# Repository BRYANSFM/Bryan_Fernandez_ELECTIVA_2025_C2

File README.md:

# Bryan_Fernandez_ELECTIVA_2025_C2

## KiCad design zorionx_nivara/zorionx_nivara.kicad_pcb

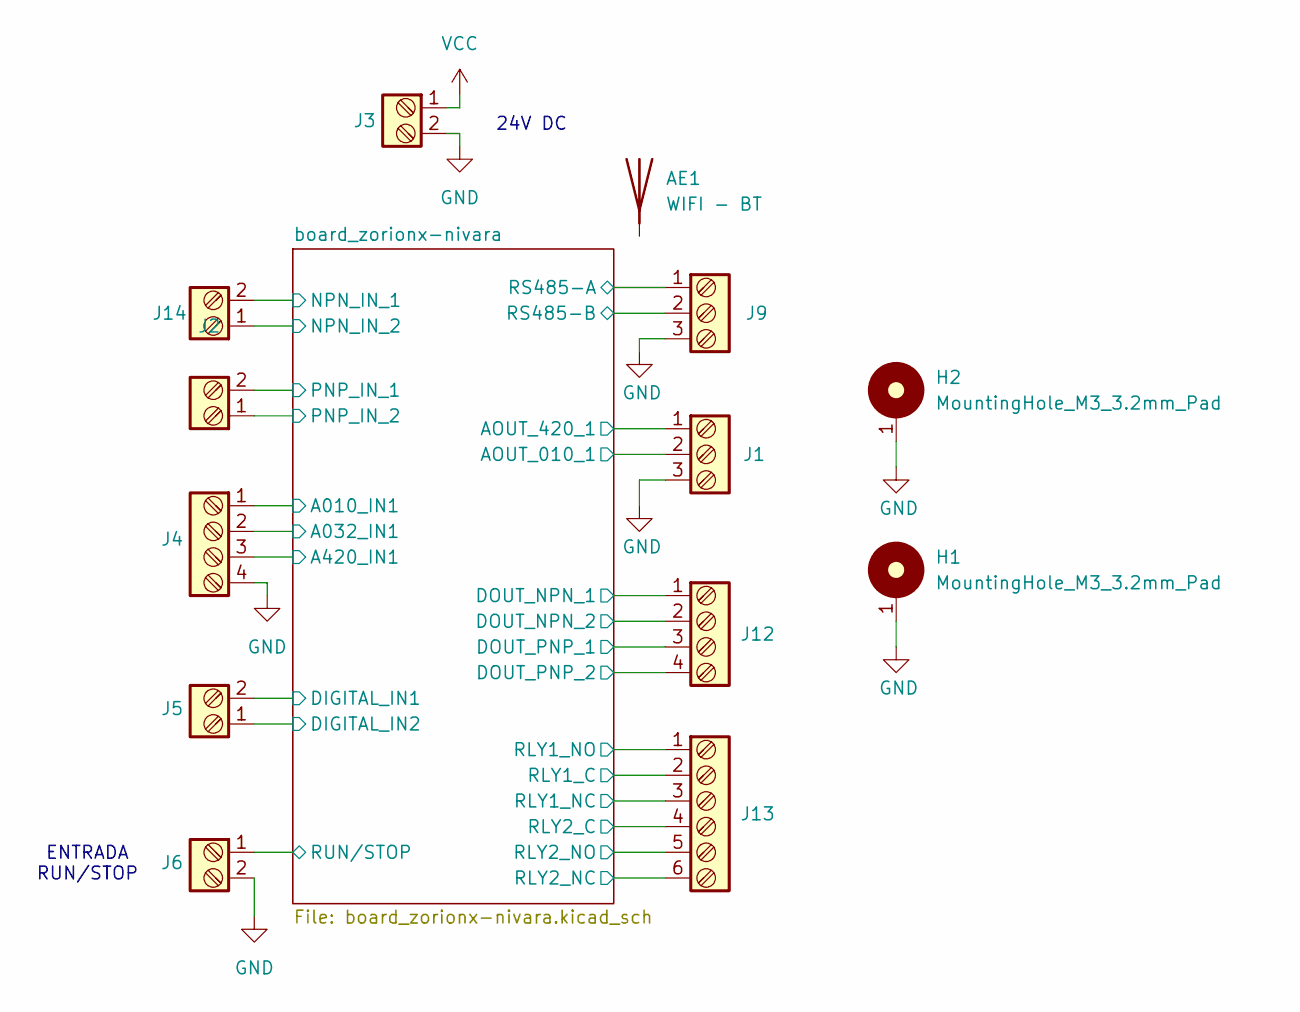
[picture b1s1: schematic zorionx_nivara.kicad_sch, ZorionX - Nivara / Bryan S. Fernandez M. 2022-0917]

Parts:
AE1: WIFI - BT
H1, H2: MountingHole_M3_3.2mm_Pad; MountingHole_3.2mm_Pad
J1: Salidas Analogicas; TerminalBlock_Phoenix_PT-1,5-3-5.0-H_1x03_P5.00mm_Horizontal
J2: Entrada PNP; TerminalBlock_Phoenix_PT-1,5-2-5.0-H_1x02_P5.00mm_Horizontal
J3: Alimentacion; TerminalBlock_Phoenix_PT-1,5-2-5.0-H_1x02_P5.00mm_Horizontal
J4: Entradas Analogicas; TerminalBlock_Phoenix_PT-1,5-4-5.0-H_1x04_P5.00mm_Horizontal
J5: Entradas digitales; TerminalBlock_Phoenix_PT-1,5-2-5.0-H_1x02_P5.00mm_Horizontal
J6: RUN/STOP; TerminalBlock_Phoenix_PT-1,5-2-5.0-H_1x02_P5.00mm_Horizontal
J9: RS-485; TerminalBlock_Phoenix_PT-1,5-3-5.0-H_1x03_P5.00mm_Horizontal
J12: Salidas NPN/PNP; TerminalBlock_Phoenix_PT-1,5-4-5.0-H_1x04_P5.00mm_Horizontal
J13: Reles; TerminalBlock_Phoenix_PT-1,5-6-5.0-H_1x06_P5.00mm_Horizontal
J14: Entrada NPN; TerminalBlock_Phoenix_PT-1,5-2-5.0-H_1x02_P5.00mm_Horizontal

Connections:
/board_zorionx-nivara/A010_IN1: J4.1; also elsewhere on the board
/board_zorionx-nivara/A032_IN1: J4.2; also elsewhere on the board
/board_zorionx-nivara/A420_IN1: J4.3; also elsewhere on the board
/board_zorionx-nivara/AOUT_010_1: J1.2; also elsewhere on the board
/board_zorionx-nivara/AOUT_420_1: J1.1; also elsewhere on the board
/board_zorionx-nivara/DIGITAL_IN1: J5.2; also elsewhere on the board
/board_zorionx-nivara/DIGITAL_IN2: J5.1; also elsewhere on the board
/board_zorionx-nivara/DOUT_NPN_1: J12.1; also elsewhere on the board
/board_zorionx-nivara/DOUT_NPN_2: J12.2; also elsewhere on the board
/board_zorionx-nivara/DOUT_PNP_1: J12.3; also elsewhere on the board
/board_zorionx-nivara/DOUT_PNP_2: J12.4; also elsewhere on the board
/board_zorionx-nivara/NPN_IN_1: J14.2; also elsewhere on the board
/board_zorionx-nivara/NPN_IN_2: J14.1; also elsewhere on the board
/board_zorionx-nivara/PNP_IN_1: J2.2; also elsewhere on the board
/board_zorionx-nivara/PNP_IN_2: J2.1; also elsewhere on the board
/board_zorionx-nivara/RLY1_C: J13.2; also elsewhere on the board
/board_zorionx-nivara/RLY1_NC: J13.3; also elsewhere on the board
/board_zorionx-nivara/RLY1_NO: J13.1; also elsewhere on the board
/board_zorionx-nivara/RLY2_C: J13.4; also elsewhere on the board
/board_zorionx-nivara/RLY2_NC: J13.6; also elsewhere on the board
/board_zorionx-nivara/RLY2_NO: J13.5; also elsewhere on the board
/board_zorionx-nivara/RS485-A: J9.1; also elsewhere on the board
/board_zorionx-nivara/RS485-B: J9.2; also elsewhere on the board
/board_zorionx-nivara/RUN/STOP: J6.1; also elsewhere on the board
GND: H1.1, H2.1, J1.3, J3.2, J4.4, J6.2, J9.3; also elsewhere on the board
VCC: J3.1; also elsewhere on the board

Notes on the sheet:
ENTRADA RUN/STOP
24V DC

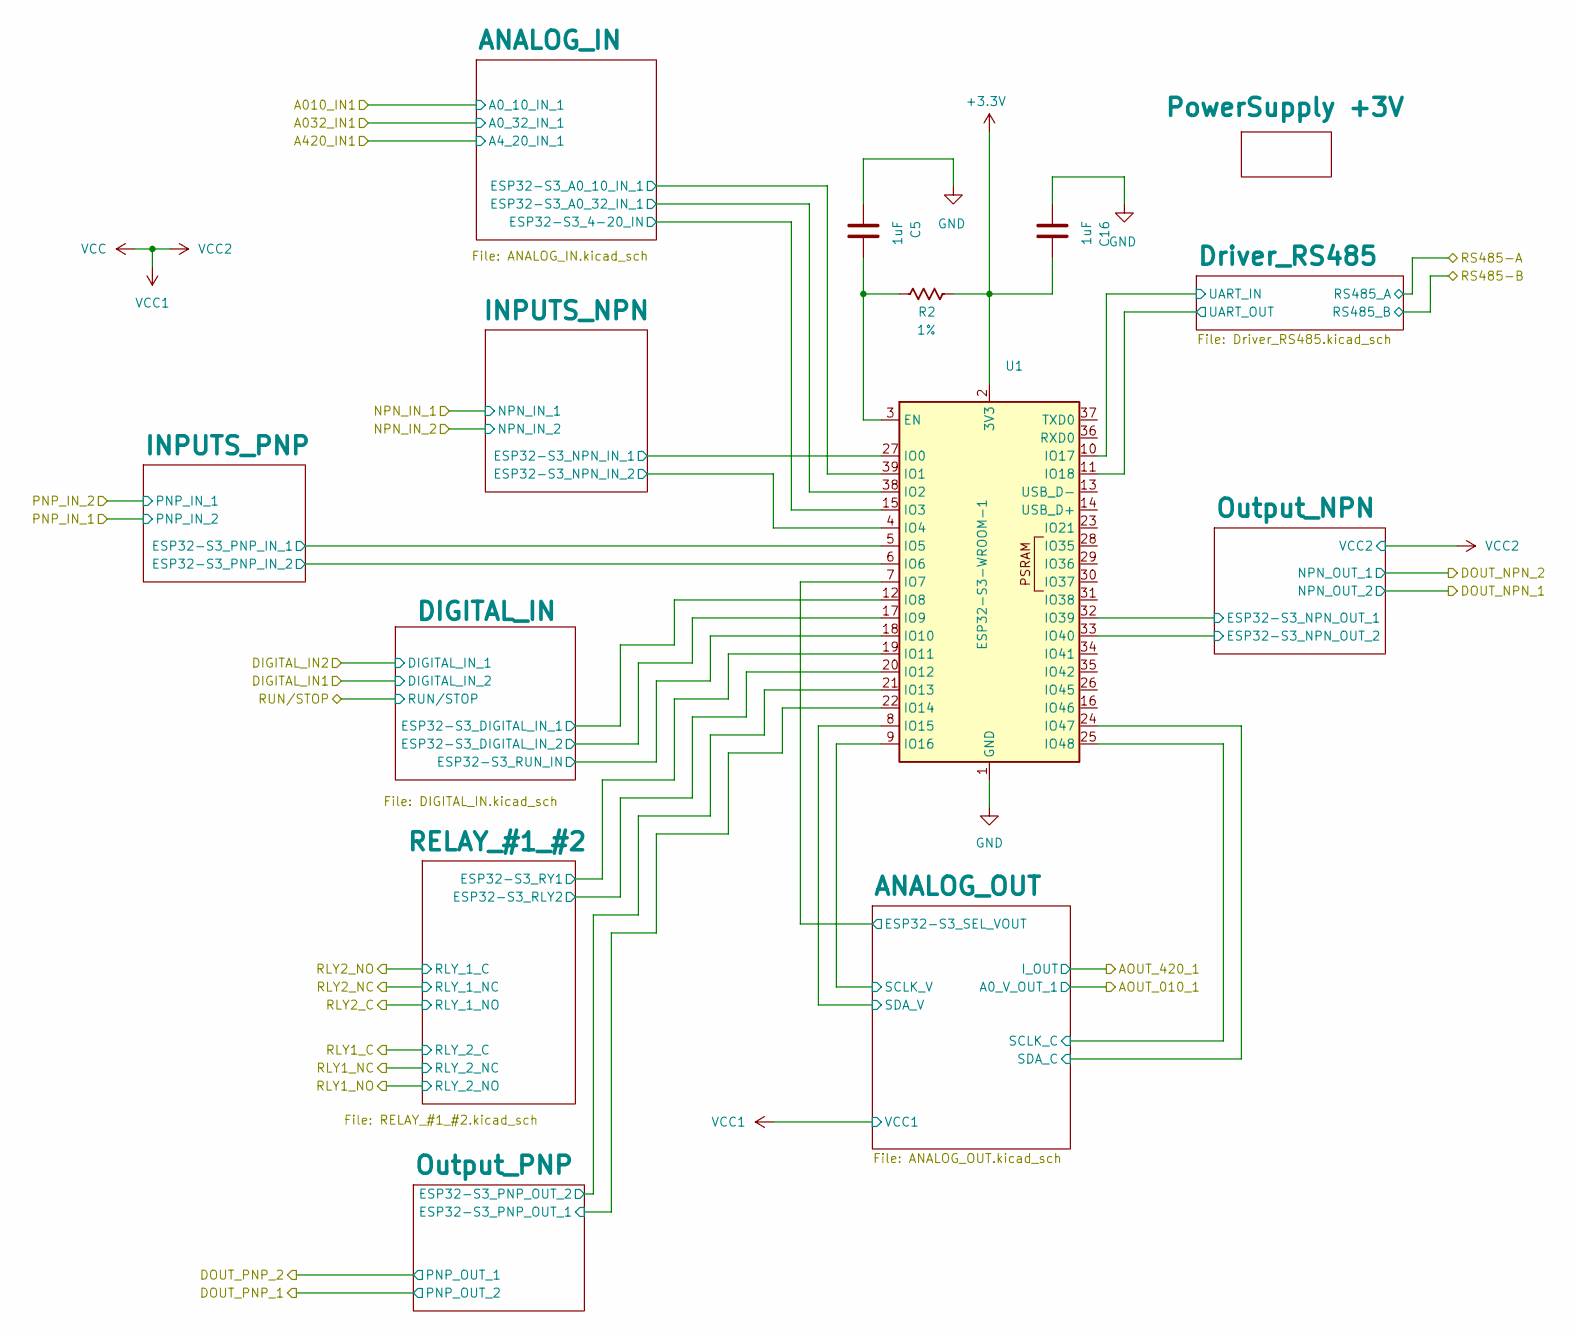
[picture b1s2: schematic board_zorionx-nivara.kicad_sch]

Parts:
C5, C16: 1uF; C_0603_1608Metric
R2: R_0603_1608Metric; Tolerancia 1%
U1: ESP32-S3-WROOM-1

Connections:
+3.3V: C16.1, R2.1, U1.2 (3V3); also elsewhere on the board
/board_zorionx-nivara/ANALOG_IN/ESP32-S3_4-20_IN: U1.15 (IO3); also elsewhere on the board
/board_zorionx-nivara/ANALOG_IN/ESP32-S3_A0_10_IN_1: U1.39 (IO1); also elsewhere on the board
/board_zorionx-nivara/ANALOG_IN/ESP32-S3_A0_32_IN_1: U1.38 (IO2); also elsewhere on the board
/board_zorionx-nivara/ANALOG_OUT/ESP32-S3_SEL_VOUT: U1.7 (IO7); also elsewhere on the board
/board_zorionx-nivara/ANALOG_OUT/SCLK_C: U1.25 (IO48); also elsewhere on the board
/board_zorionx-nivara/ANALOG_OUT/SCLK_V: U1.9 (IO16); also elsewhere on the board
/board_zorionx-nivara/ANALOG_OUT/SDA_C: U1.24 (IO47); also elsewhere on the board
/board_zorionx-nivara/ANALOG_OUT/SDA_V: U1.8 (IO15); also elsewhere on the board
/board_zorionx-nivara/DIGITAL_IN/ESP32-S3_DIGITAL_IN_1: U1.12 (IO8); also elsewhere on the board
/board_zorionx-nivara/DIGITAL_IN/ESP32-S3_DIGITAL_IN_2: U1.17 (IO9); also elsewhere on the board
/board_zorionx-nivara/DIGITAL_IN/ESP32-S3_RUN_IN: U1.18 (IO10); also elsewhere on the board
/board_zorionx-nivara/Driver_RS485/UART_IN: U1.10 (IO17); also elsewhere on the board
/board_zorionx-nivara/Driver_RS485/UART_OUT: U1.11 (IO18); also elsewhere on the board
/board_zorionx-nivara/INPUTS_NPN/ESP32-S3_NPN_IN_1: U1.27 (IO0); also elsewhere on the board
/board_zorionx-nivara/INPUTS_NPN/ESP32-S3_NPN_IN_2: U1.4 (IO4); also elsewhere on the board
/board_zorionx-nivara/INPUTS_PNP/ESP32-S3_PNP_IN_1: U1.5 (IO5); also elsewhere on the board
/board_zorionx-nivara/INPUTS_PNP/ESP32-S3_PNP_IN_2: U1.6 (IO6); also elsewhere on the board
/board_zorionx-nivara/Output_NPN/ESP32-S3_NPN_OUT_1: U1.32 (IO39); also elsewhere on the board
/board_zorionx-nivara/Output_NPN/ESP32-S3_NPN_OUT_2: U1.33 (IO40); also elsewhere on the board
/board_zorionx-nivara/Output_PNP/ESP32-S3_PNP_OUT_1: U1.22 (IO14); also elsewhere on the board
/board_zorionx-nivara/Output_PNP/ESP32-S3_PNP_OUT_2: U1.21 (IO13); also elsewhere on the board
/board_zorionx-nivara/RELAY_#1_#2/ESP32-S3_RLY2: U1.20 (IO12); also elsewhere on the board
/board_zorionx-nivara/RELAY_#1_#2/ESP32-S3_RY1: U1.19 (IO11); also elsewhere on the board
GND: C5.2, C16.2, U1.1 (GND), U1.40 (GND), U1.41 (GND); also elsewhere on the board
unnamed: C5.1, R2.2, U1.3 (EN)

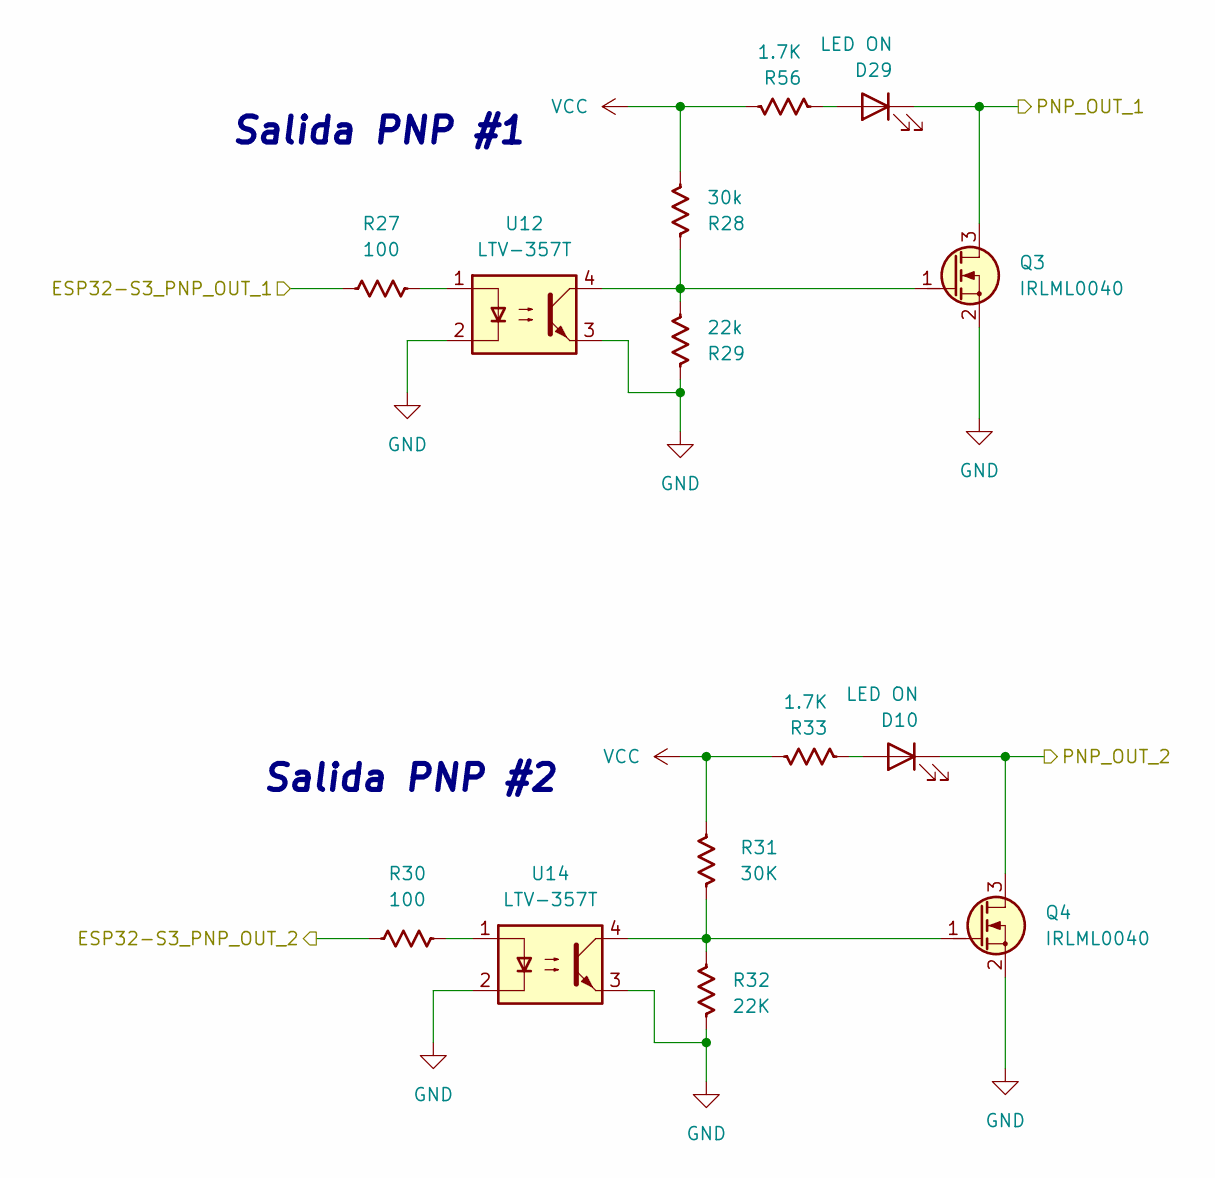
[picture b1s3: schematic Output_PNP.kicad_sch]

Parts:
D10, D29: LED ON; LED_0603_1608Metric
Q3, Q4: IRLML0040; SOT-23
R27, R30: 100; R_0603_1608Metric
R28: 30k; R_0603_1608Metric
R29: 22k; R_0603_1608Metric
R31: 30K; R_0603_1608Metric
R32: 22K; R_0603_1608Metric
R33, R56: 1.7K; R_0603_1608Metric
U12, U14: LTV-357T; SO-4_4.4x3.6mm_P2.54mm

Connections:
/board_zorionx-nivara/DOUT_PNP_1: D10.1 (K), Q4.3 (D); also elsewhere on the board
/board_zorionx-nivara/DOUT_PNP_2: D29.1 (K), Q3.3 (D); also elsewhere on the board
/board_zorionx-nivara/Output_PNP/ESP32-S3_PNP_OUT_1: R27.1; also elsewhere on the board
/board_zorionx-nivara/Output_PNP/ESP32-S3_PNP_OUT_2: R30.1; also elsewhere on the board
GND: Q3.2 (S), Q4.2 (S), R29.1, R32.1, U12.2, U12.3, U14.2, U14.3; also elsewhere on the board
unnamed: D10.2 (A), R33.2
unnamed: D29.2 (A), R56.2
unnamed: Q3.1 (G), R28.1, R29.2, U12.4
unnamed: Q4.1 (G), R31.1, R32.2, U14.4
unnamed: R27.2, U12.1
unnamed: R30.2, U14.1
VCC: R28.2, R31.2, R33.1, R56.1; also elsewhere on the board

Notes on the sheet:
Salida PNP #1
Salida PNP #2

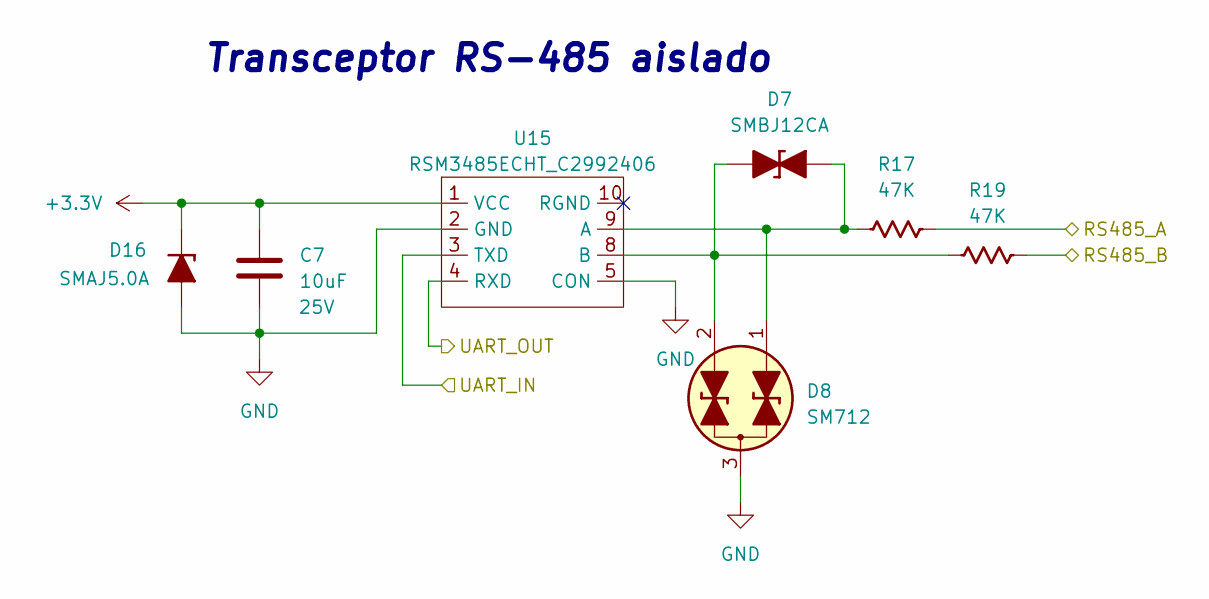
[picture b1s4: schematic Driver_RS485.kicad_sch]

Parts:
C7: 10uF; C_0603_1608Metric
D7: SMBJ12CA; D_SMB_TVS
D8: SM712; SOT-23
D16: SMAJ5.0A; D_SMA
R17, R19: 47K; R_0603_1608Metric
U15: RSM3485ECHT_C2992406; YLPTEC RSM3485ECHT

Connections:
+3.3V: C7.1, D16.1 (K), U15.1 (VCC); also elsewhere on the board
/board_zorionx-nivara/Driver_RS485/UART_IN: U15.3 (TXD); also elsewhere on the board
/board_zorionx-nivara/Driver_RS485/UART_OUT: U15.4 (RXD); also elsewhere on the board
/board_zorionx-nivara/RS485-A: R17.2; also elsewhere on the board
/board_zorionx-nivara/RS485-B: R19.2; also elsewhere on the board
GND: C7.2, D8.3 (Com), D16.2 (A), U15.2 (GND), U15.5 (CON); also elsewhere on the board
unnamed: D7.2 (A), D8.1 (A1), R17.1, U15.9 (A)
unnamed: D7.1 (K), D8.2 (A2), R19.1, U15.8 (B)

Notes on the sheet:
Transceptor RS-485 aislado

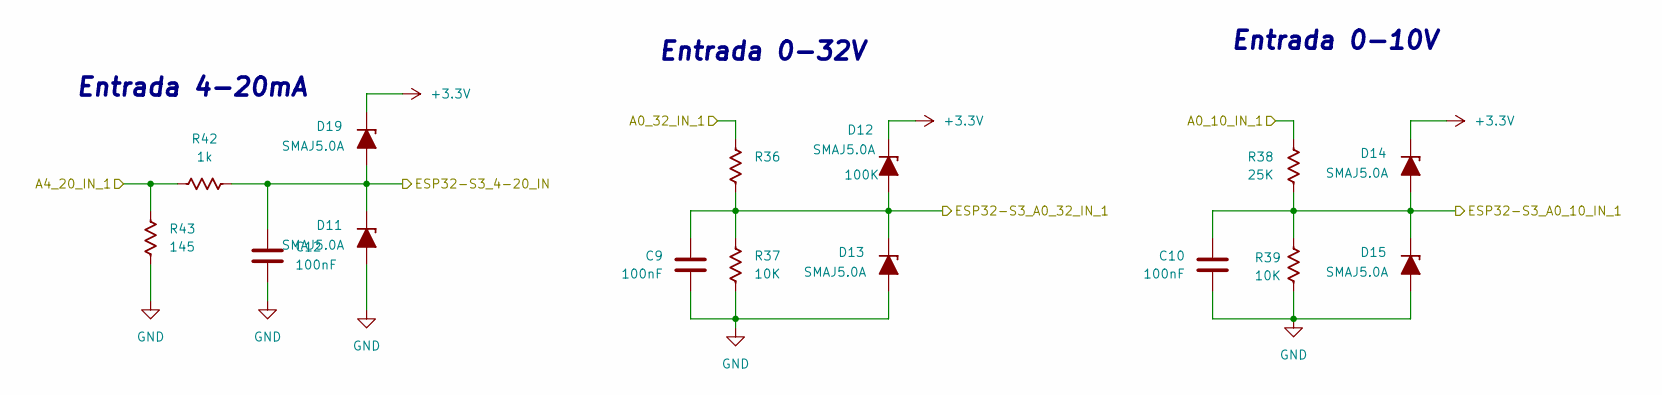
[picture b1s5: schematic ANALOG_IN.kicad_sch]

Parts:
C9, C10, C12: 100nF; C_0603_1608Metric; Voltage 10V
D11, D12, D13, D14, D15, D19: SMAJ5.0A; D_SMA
R36: 100K; R_0603_1608Metric
R37, R39: 10K; R_0603_1608Metric
R38: 25K; R_0603_1608Metric
R42: 1k; R_0603_1608Metric
R43: 145; R_0805_2012Metric

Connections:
+3.3V: D12.1 (K), D14.1 (K), D19.1 (K); also elsewhere on the board
/board_zorionx-nivara/A010_IN1: R38.2; also elsewhere on the board
/board_zorionx-nivara/A032_IN1: R36.2; also elsewhere on the board
/board_zorionx-nivara/A420_IN1: R42.1, R43.1; also elsewhere on the board
/board_zorionx-nivara/ANALOG_IN/ESP32-S3_4-20_IN: C12.1, D11.1 (K), D19.2 (A), R42.2; also elsewhere on the board
/board_zorionx-nivara/ANALOG_IN/ESP32-S3_A0_10_IN_1: C10.1, D14.2 (A), D15.1 (K), R38.1, R39.2; also elsewhere on the board
/board_zorionx-nivara/ANALOG_IN/ESP32-S3_A0_32_IN_1: C9.1, D12.2 (A), D13.1 (K), R36.1, R37.2; also elsewhere on the board
GND: C9.2, C10.2, C12.2, D11.2 (A), D13.2 (A), D15.2 (A), R37.1, R39.1, R43.2; also elsewhere on the board

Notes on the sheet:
Entrada 0-10V
Entrada 0-32V
Entrada 4-20mA

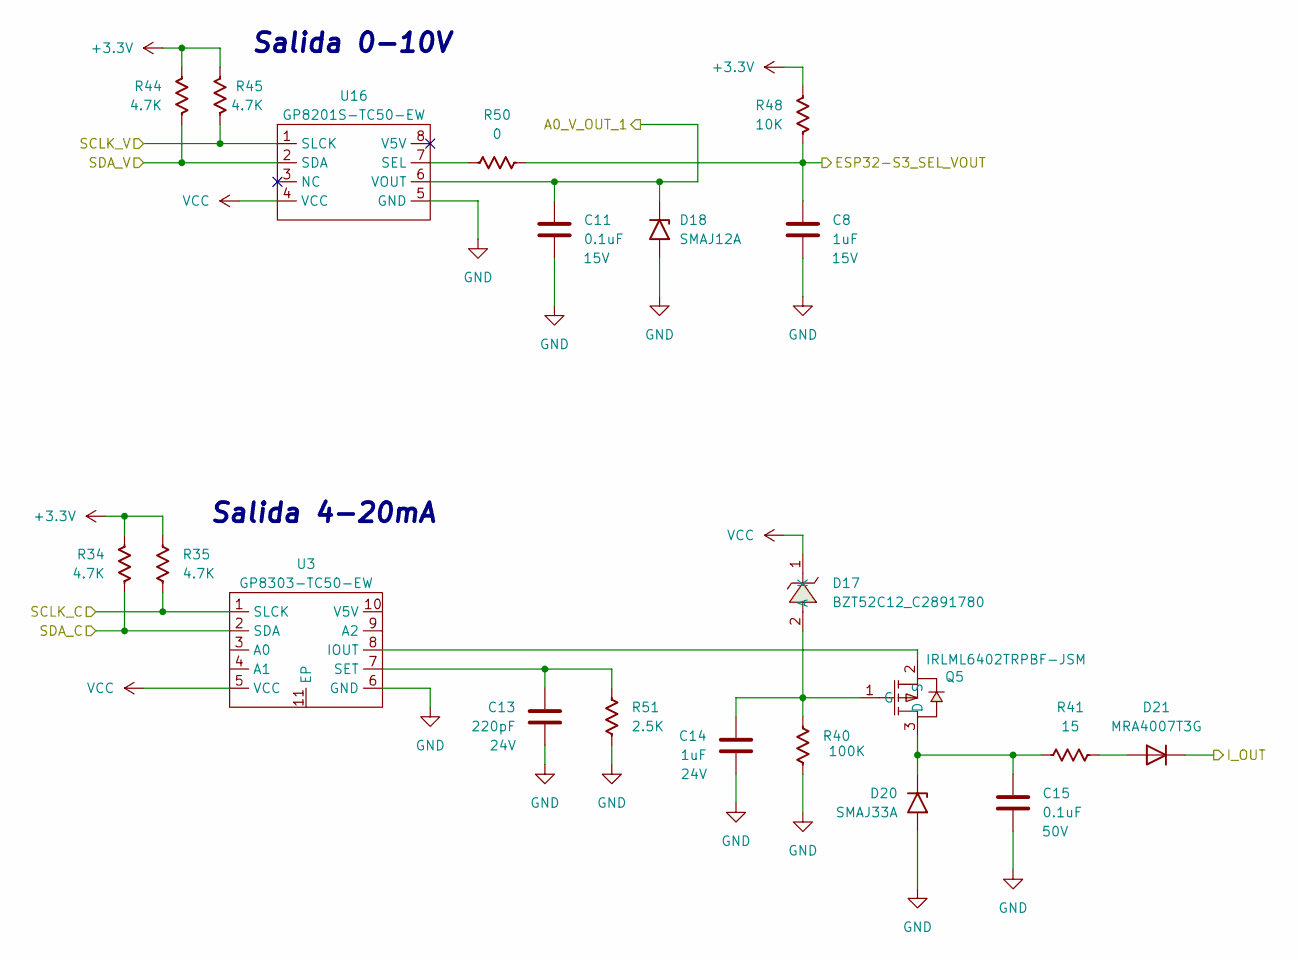
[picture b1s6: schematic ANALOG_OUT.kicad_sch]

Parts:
C8, C14: 1uF; C_0603_1608Metric
C11, C15: 0.1uF; C_0603_1608Metric
C13: 220pF; C_0603_1608Metric
D17: BZT52C12_C2891780; D_SOD-123; LCSC Part C2891780
D18: SMAJ12A; D_SMA
D20: SMAJ33A; D_SMA
D21: MRA4007T3G; D_SMA
Q5: IRLML6402TRPBF-JSM; SOT-23; LCSC Part C18190991
R34, R35, R44, R45: 4.7K; R_0603_1608Metric
R40: 100K; R_0603_1608Metric
R41: 15; R_0805_2012Metric
R48: 10K; R_0603_1608Metric
R50: 0; R_0603_1608Metric
R51: 2.5K; R_0603_1608Metric
U3: GP8303-TC50-EW; SSOP-10_3.9x4.9mm_P1.00mm
U16: GP8201S-TC50-EW; SSOP-8_3.95x5.21x3.27mm_P1.27mm

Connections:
+3.3V: R34.1, R35.1, R44.1, R45.1, R48.1; also elsewhere on the board
/board_zorionx-nivara/ANALOG_OUT/ESP32-S3_SEL_VOUT: C8.1, R48.2, R50.2; also elsewhere on the board
/board_zorionx-nivara/ANALOG_OUT/SCLK_C: R35.2, U3.1 (SLCK); also elsewhere on the board
/board_zorionx-nivara/ANALOG_OUT/SCLK_V: R45.2, U16.1 (SLCK); also elsewhere on the board
/board_zorionx-nivara/ANALOG_OUT/SDA_C: R34.2, U3.2 (SDA); also elsewhere on the board
/board_zorionx-nivara/ANALOG_OUT/SDA_V: R44.2, U16.2 (SDA); also elsewhere on the board
/board_zorionx-nivara/AOUT_010_1: C11.1, D18.1 (A1), U16.6 (VOUT); also elsewhere on the board
/board_zorionx-nivara/AOUT_420_1: D21.1 (K); also elsewhere on the board
GND: C8.2, C11.2, C13.2, C14.2, C15.2, D18.2 (A2), D20.2 (A2), R40.2, R51.2, U3.6 (GND), U16.5 (GND); also elsewhere on the board
unnamed: C14.1, D17.2 (A), Q5.1 (G), R40.1
unnamed: C15.1, D20.1 (A1), Q5.3 (D), R41.1
unnamed: D21.2 (A), R41.2
unnamed: Q5.2 (S), U3.8 (IOUT)
unnamed: C13.1, R51.1, U3.7 (SET)
unnamed: R50.1, U16.7 (SEL)
VCC: D17.1 (K), U3.5 (VCC), U16.4 (VCC); also elsewhere on the board

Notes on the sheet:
Salida 0-10V
Salida 4-20mA

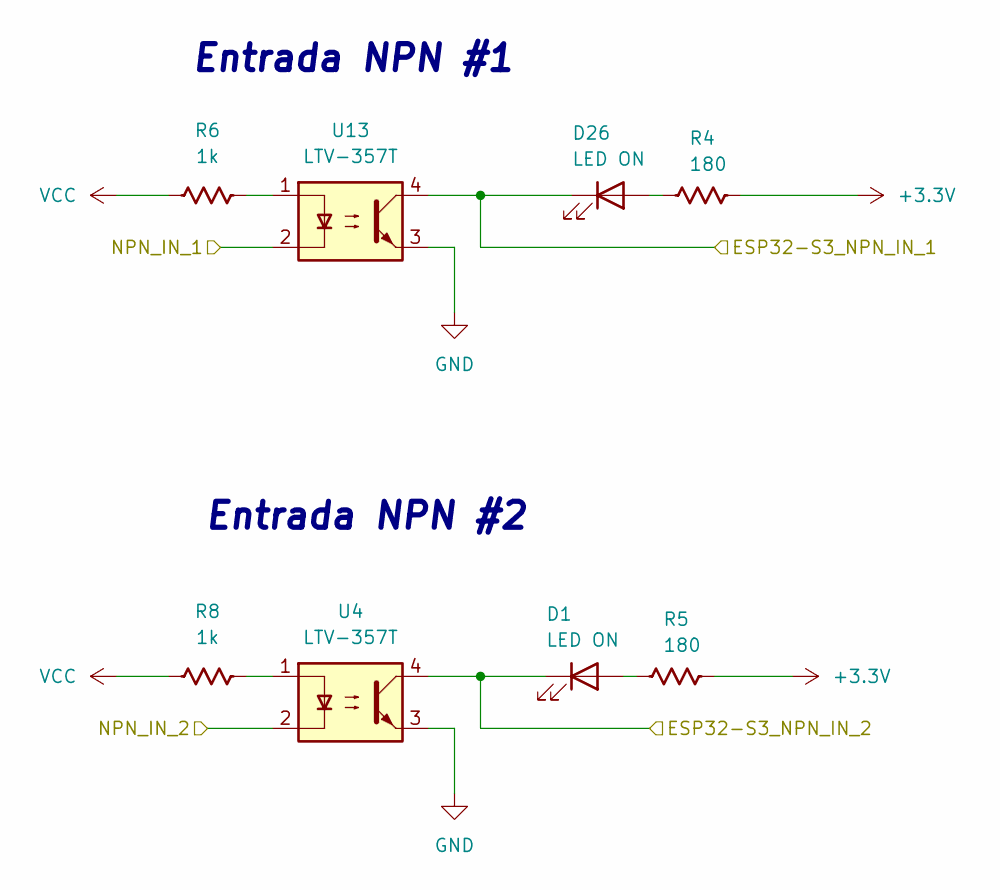
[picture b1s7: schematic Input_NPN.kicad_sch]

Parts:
D1, D26: LED ON; LED_0603_1608Metric
R4, R5: 180; R_0603_1608Metric
R6, R8: 1k; R_0603_1608Metric
U4, U13: LTV-357T; SO-4_4.4x3.6mm_P2.54mm

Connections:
+3.3V: R4.1, R5.1; also elsewhere on the board
/board_zorionx-nivara/INPUTS_NPN/ESP32-S3_NPN_IN_1: D26.1 (K), U13.4; also elsewhere on the board
/board_zorionx-nivara/INPUTS_NPN/ESP32-S3_NPN_IN_2: D1.1 (K), U4.4; also elsewhere on the board
/board_zorionx-nivara/NPN_IN_1: U13.2; also elsewhere on the board
/board_zorionx-nivara/NPN_IN_2: U4.2; also elsewhere on the board
GND: U4.3, U13.3; also elsewhere on the board
unnamed: D1.2 (A), R5.2
unnamed: D26.2 (A), R4.2
unnamed: R6.2, U13.1
unnamed: R8.2, U4.1
VCC: R6.1, R8.1; also elsewhere on the board

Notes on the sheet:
Entrada NPN #2
Entrada NPN #1

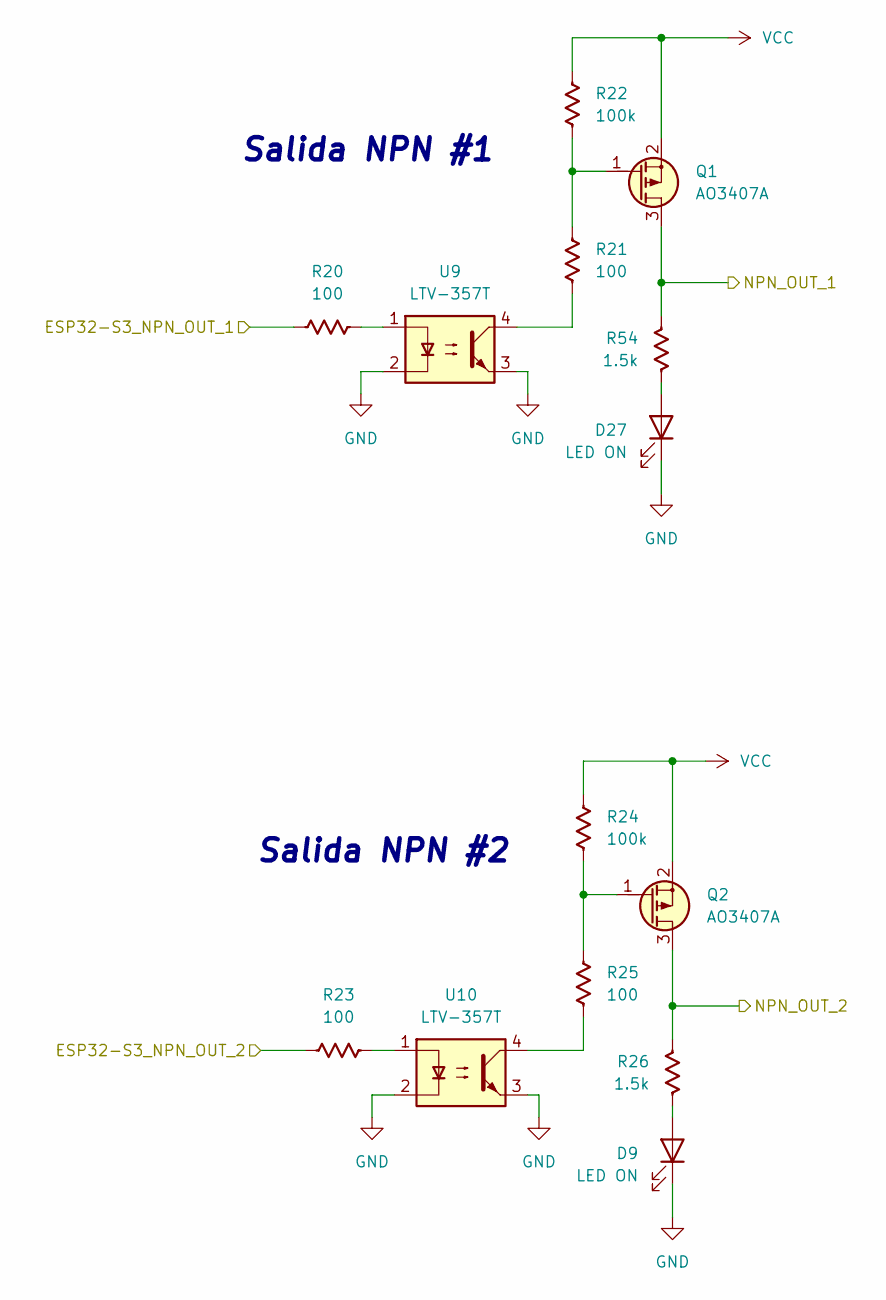
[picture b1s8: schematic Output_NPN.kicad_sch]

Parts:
D9, D27: LED ON; LED_0603_1608Metric
Q1, Q2: AO3407A; SOT-23
R20, R21, R23, R25: 100; R_0603_1608Metric
R22, R24: 100k; R_0603_1608Metric
R26, R54: 1.5k; R_0603_1608Metric
U9, U10: LTV-357T; SO-4_4.4x3.6mm_P2.54mm

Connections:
/board_zorionx-nivara/DOUT_NPN_1: Q2.3 (D), R26.1; also elsewhere on the board
/board_zorionx-nivara/DOUT_NPN_2: Q1.3 (D), R54.1; also elsewhere on the board
/board_zorionx-nivara/Output_NPN/ESP32-S3_NPN_OUT_1: R20.1; also elsewhere on the board
/board_zorionx-nivara/Output_NPN/ESP32-S3_NPN_OUT_2: R23.1; also elsewhere on the board
GND: D9.1 (K), D27.1 (K), U9.2, U9.3, U10.2, U10.3; also elsewhere on the board
unnamed: D9.2 (A), R26.2
unnamed: D27.2 (A), R54.2
unnamed: Q1.1 (G), R21.1, R22.2
unnamed: Q2.1 (G), R24.2, R25.1
unnamed: R20.2, U9.1
unnamed: R21.2, U9.4
unnamed: R23.2, U10.1
unnamed: R25.2, U10.4
VCC: Q1.2 (S), Q2.2 (S), R22.1, R24.1; also elsewhere on the board

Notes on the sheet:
Salida NPN #1
Salida NPN #2

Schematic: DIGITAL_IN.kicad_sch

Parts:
D4, D5, D6: LED ON; LED_0603_1608Metric
R12, R13, R15: 180; R_0603_1608Metric
R14, R16, R18: 1k; R_0603_1608Metric
U7, U8, U11: LTV-357T; SO-4_4.4x3.6mm_P2.54mm

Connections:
+3.3V: R12.1, R13.1, R15.1; also elsewhere on the board
/board_zorionx-nivara/DIGITAL_IN1: R14.1; also elsewhere on the board
/board_zorionx-nivara/DIGITAL_IN2: R16.1; also elsewhere on the board
/board_zorionx-nivara/DIGITAL_IN/ESP32-S3_DIGITAL_IN_1: D4.1 (K), U11.4; also elsewhere on the board
/board_zorionx-nivara/DIGITAL_IN/ESP32-S3_DIGITAL_IN_2: D5.1 (K), U7.4; also elsewhere on the board
/board_zorionx-nivara/DIGITAL_IN/ESP32-S3_RUN_IN: D6.1 (K), U8.4; also elsewhere on the board
/board_zorionx-nivara/RUN/STOP: R18.1; also elsewhere on the board
GND: U7.2, U7.3, U8.2, U8.3, U11.2, U11.3; also elsewhere on the board
unnamed: D4.2 (A), R12.2
unnamed: D5.2 (A), R13.2
unnamed: D6.2 (A), R15.2
unnamed: R14.2, U7.1
unnamed: R16.2, U11.1
unnamed: R18.2, U8.1

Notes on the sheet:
Entrada DIGITAL #1
Entrada DIGITAL #2
RUN/STOP

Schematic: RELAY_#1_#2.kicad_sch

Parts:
K1, K3: G5LE-1; Relay_SPDT_Omron-G5LE-1
U18: LANKE LK1802; SOT-23-6

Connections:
/board_zorionx-nivara/RELAY_#1_#2/ESP32-S3_RLY2: U18.4 (2B); also elsewhere on the board
/board_zorionx-nivara/RELAY_#1_#2/ESP32-S3_RY1: U18.3 (1B); also elsewhere on the board
/board_zorionx-nivara/RLY1_C: K1.1; also elsewhere on the board
/board_zorionx-nivara/RLY1_NC: K1.4; also elsewhere on the board
/board_zorionx-nivara/RLY1_NO: K1.3; also elsewhere on the board
/board_zorionx-nivara/RLY2_C: K3.3; also elsewhere on the board
/board_zorionx-nivara/RLY2_NC: K3.4; also elsewhere on the board
/board_zorionx-nivara/RLY2_NO: K3.1; also elsewhere on the board
GND: U18.2 (E); also elsewhere on the board
unnamed: K3.5, U18.1 (1C)
unnamed: K1.2, U18.6 (2C)
VCC: K1.5, K3.2, U18.5 (COM); also elsewhere on the board

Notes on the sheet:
Controlador RELAY #1, #2

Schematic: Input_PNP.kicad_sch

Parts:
D2, D3: LED ON; LED_0603_1608Metric
R7, R9: 180; R_0603_1608Metric
R10, R11: 1k; R_0603_1608Metric
U5, U6: LTV-357T; SO-4_4.4x3.6mm_P2.54mm

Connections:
+3.3V: R7.1, R9.1; also elsewhere on the board
/board_zorionx-nivara/INPUTS_PNP/ESP32-S3_PNP_IN_1: D2.1 (K), U5.4; also elsewhere on the board
/board_zorionx-nivara/INPUTS_PNP/ESP32-S3_PNP_IN_2: D3.1 (K), U6.4; also elsewhere on the board
/board_zorionx-nivara/PNP_IN_1: R11.1; also elsewhere on the board
/board_zorionx-nivara/PNP_IN_2: R10.1; also elsewhere on the board
GND: U5.2, U5.3, U6.2, U6.3; also elsewhere on the board
unnamed: D2.2 (A), R7.2
unnamed: D3.2 (A), R9.2
unnamed: R10.2, U5.1
unnamed: R11.2, U6.1

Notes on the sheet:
Entrada PNP #1
Entrada PNP #2

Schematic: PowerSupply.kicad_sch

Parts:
C1: 100pF; C_0603_1608Metric
C2, C6: 22uF; C_0805
C3: 10uF; C_1206_3216Metric
C4: 100nF; C_0603_1608Metric
JP1: SolderJumper_2_Open; SolderJumper-2_P1.3mm_Open_RoundedPad1.0x1.5mm
L1: 6.8uH; L_Chilisin_BMRA00040420; Part number SL0624-6R8M
R1: 196K; R_0603_1608Metric; Tolerancia 1%
R3: 62K; R_0603_1608Metric; Tolerancia 1%
TP1, TP2, TP3, TP4: TestPoint; TestPoint_THTPad_D1.0mm_Drill0.5mm
U2: AP63203WU; TSOT-23-6

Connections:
+3.3V: JP1.2 (B), TP4.1; also elsewhere on the board
/board_zorionx-nivara/PowerSupply +3V/sw: C4.2, L1.2, U2.5 (SW)
/board_zorionx-nivara/PowerSupply +3V/vout: C1.1, C2.1, C6.1, JP1.1 (A), L1.1, R1.1, TP1.1
GND: C2.2, C3.2, C6.2, R3.2, U2.4 (GND); also elsewhere on the board
unnamed: C4.1, U2.6 (BST)
unnamed: C1.2, R1.2, R3.1, TP2.1, U2.1 (FB)
VCC: C3.1, TP3.1, U2.2 (EN), U2.3 (IN); also elsewhere on the board

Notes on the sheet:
ic AP63203
Regulador 3.3V

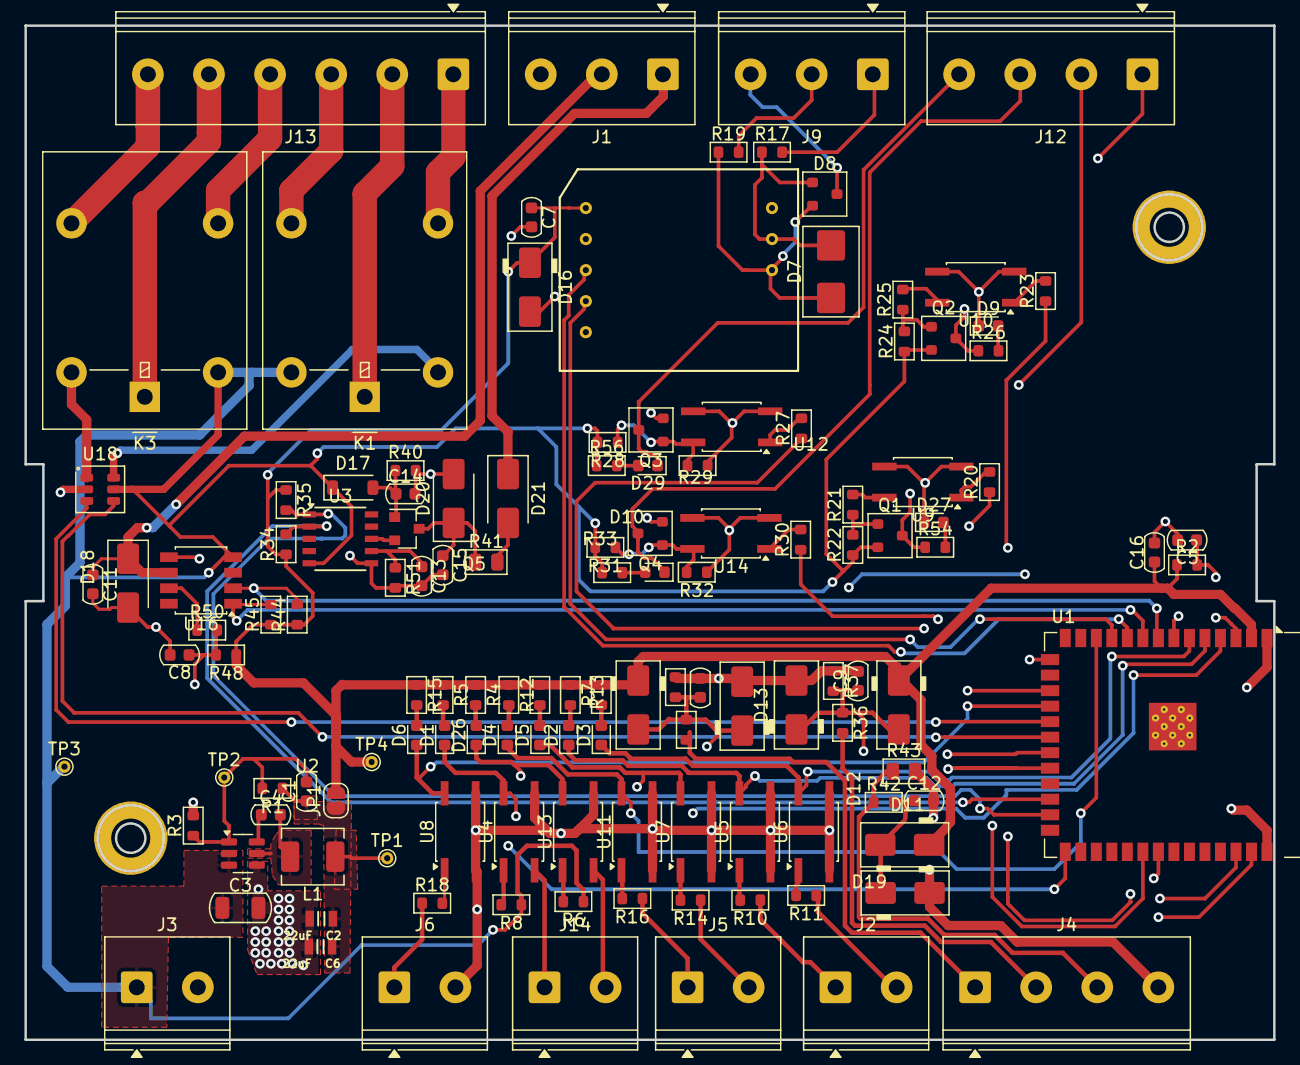
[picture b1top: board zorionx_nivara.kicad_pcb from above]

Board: 4 copper layers, 102.2 x 83.0 mm, 132 parts (0 on the bottom side), 93 nets.

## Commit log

2025-07-11 Primer commit local
2025-07-11 Primer commit
2025-07-11 Primer commit 2
2025-07-11 Agregar respaldos
2025-07-16 ultimo commit 1
2025-07-16 Salvado
2025-07-16 Salvado1
2025-07-17 Salvado2
2025-08-15 Enrutando
2025-08-22 Enrutando_finalizando1
2025-08-22 Enrutando_finalizado2
